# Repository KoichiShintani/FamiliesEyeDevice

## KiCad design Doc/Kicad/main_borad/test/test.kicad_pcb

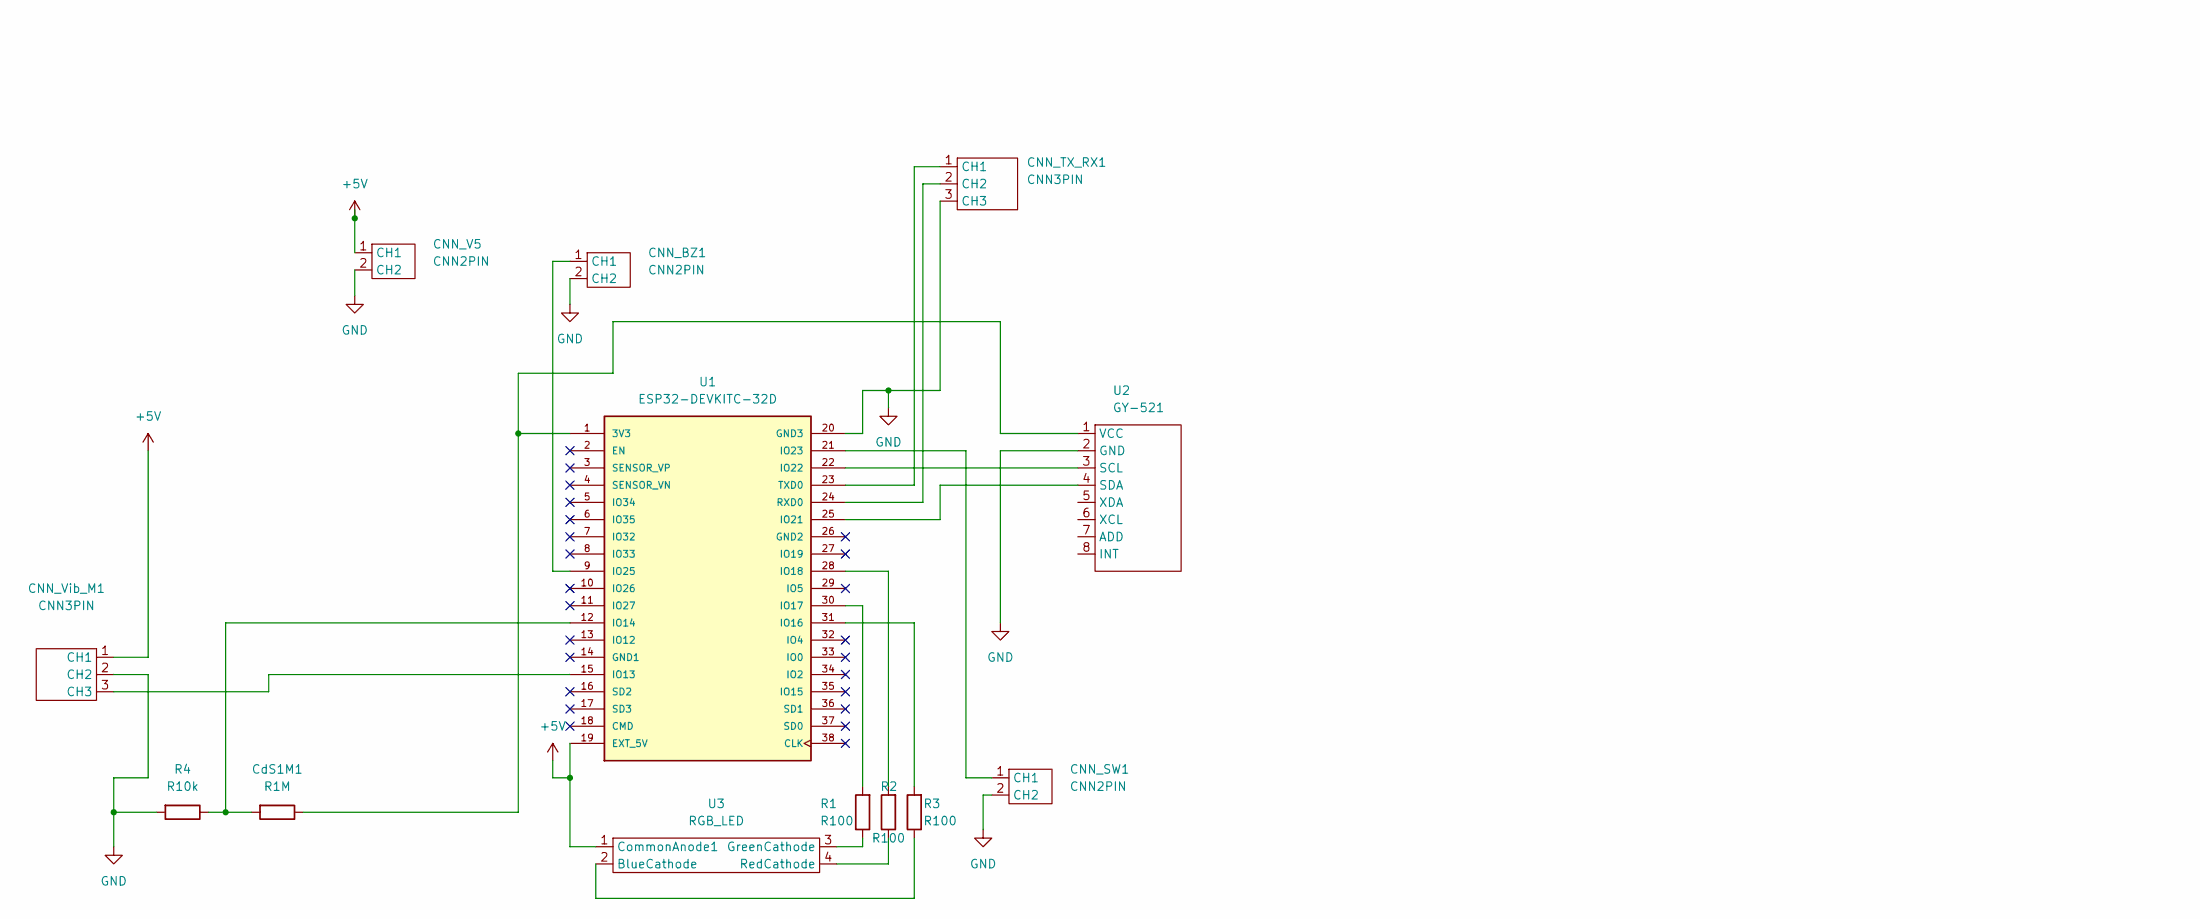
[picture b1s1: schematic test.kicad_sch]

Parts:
CNN_BZ1: CNN2PIN; SIP-2
CNN_SW1: CNN2PIN; SIP-2
CNN_TX_RX1: CNN3PIN; SIP-3
CNN_V5: CNN2PIN; SIP-2
CNN_Vib_M1: CNN3PIN; SIP-3
CdS1M1: R1M; SIP-2
R1, R2, R3: R100; SIP-2
R4: R10k; SIP-2
U1: ESP32-DEVKITC-32D; MODULE_ESP32-DEVKITC-32D; PARTREV 4
U2: GY-521; SIP-8
U3: RGB_LED; DIP-4_200_ELL

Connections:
+5V: CNN_V5.1 (CH1), CNN_Vib_M1.1 (CH1), U1.19 (EXT_5V), U3.1 (CommonAnode1)
GND: CNN_BZ1.2 (CH2), CNN_SW1.2 (CH2), CNN_TX_RX1.3 (CH3), CNN_V5.2 (CH2), CNN_Vib_M1.2 (CH2), R4.2, U1.20 (GND3), U2.2 (GND)
unnamed: CNN_TX_RX1.1 (CH1), U1.23 (TXD0)
unnamed: CNN_TX_RX1.2 (CH2), U1.24 (RXD0)
unnamed: CdS1M1.1, U1.1 (3V3), U2.1 (VCC)
unnamed: R1.2, U1.30 (IO17)
unnamed: R2.2, U1.28 (IO18)
unnamed: R3.2, U1.31 (IO16)
unnamed: CNN_BZ1.1 (CH1), U1.9 (IO25)
unnamed: CdS1M1.2, R4.1, U1.12 (IO14)
unnamed: CNN_Vib_M1.3 (CH3), U1.15 (IO13)
unnamed: CNN_SW1.1 (CH1), U1.21 (IO23)
unnamed: U1.22 (IO22), U2.3 (SCL)
unnamed: U1.25 (IO21), U2.4 (SDA)
unnamed: R3.1, U3.2 (BlueCathode)
unnamed: R1.1, U3.3 (GreenCathode)
unnamed: R2.1, U3.4 (RedCathode)

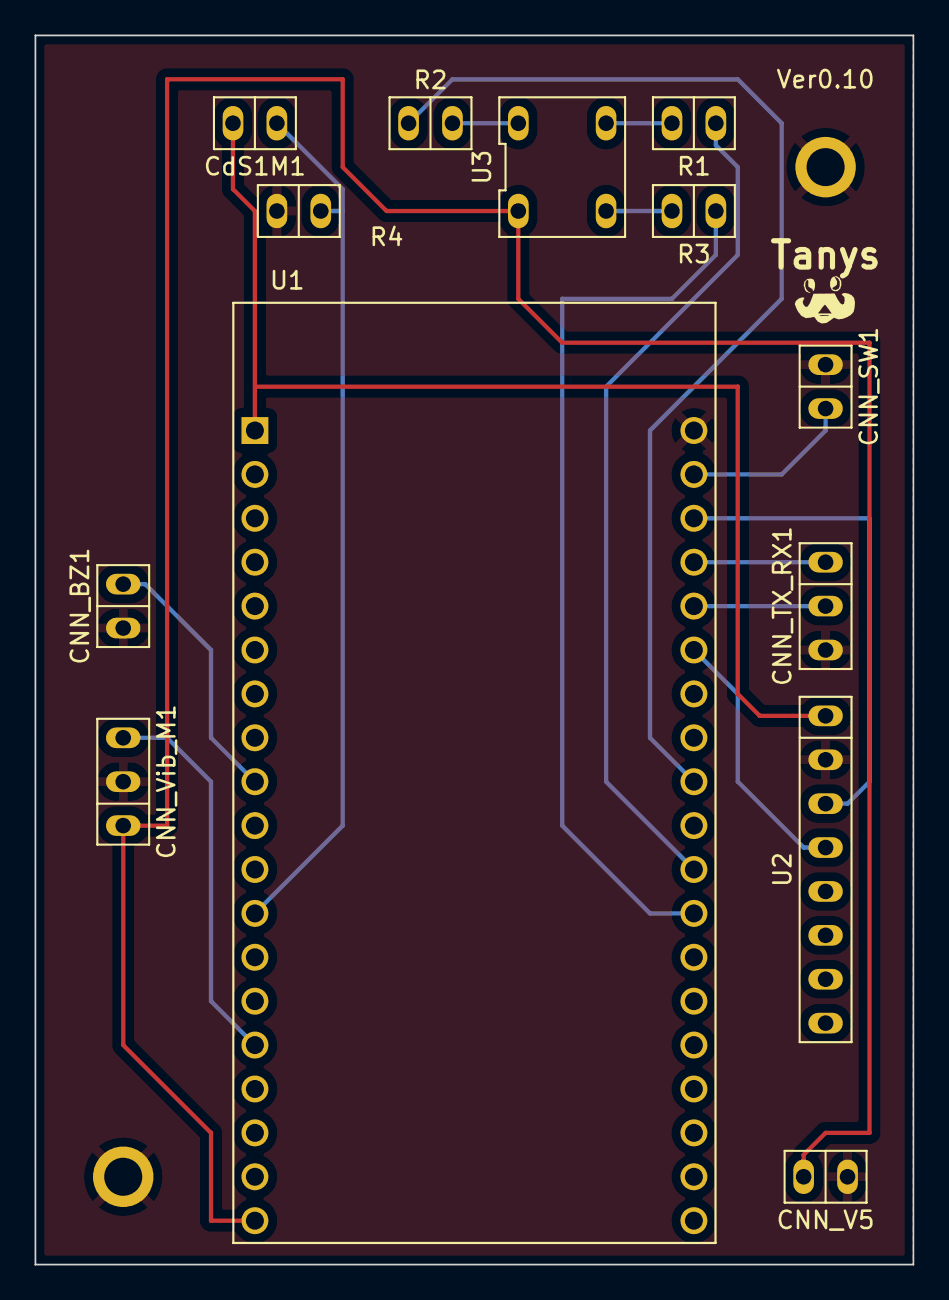
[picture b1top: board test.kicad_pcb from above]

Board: 2 copper layers, 50.8 x 71.1 mm, 13 parts (0 on the bottom side), 17 nets.

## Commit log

2022-08-10 初版をコミット
